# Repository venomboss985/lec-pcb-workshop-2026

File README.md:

# PCB Design Workshop

## Description
Learn how to use KiCad by designing your own PCB from scratch. During the workshops, you'll learn how most digital electronic devices get designed, schematic and layout best practices, and be able to assemble, test, and use your board to do something!

### What will be taught
* Basic KiCad usage
* Schematic best practices
* Layout best practices
* Using soldering irons, multimeters, and oscilloscopes

### What will NOT be taught
* Basic electrical theory (Ohms law, parallel/series, etc.)
* Firmware development (if firmware is needed, it will be provided)
* Datasheets (covered, not in depth)

## Prerequisites
* Some basic electrical knowledge (1 yr electrical or active LEC member)
* A laptop >4GB RAM with KiCad preinstalled
* git or GitHub Desktop and a GitHub account

## Rough Schedule
* Day 1 (3-4 hrs, hybrid): Anatomy of a PCB (by making a keychain light)
* Day 2 (3-4 hrs, hybrid): Project design (Start and hopefully finish the chosen project)
* Day 3 (2-3 hrs, in-person): Assemble and test your board (firmware will be provided if needed)

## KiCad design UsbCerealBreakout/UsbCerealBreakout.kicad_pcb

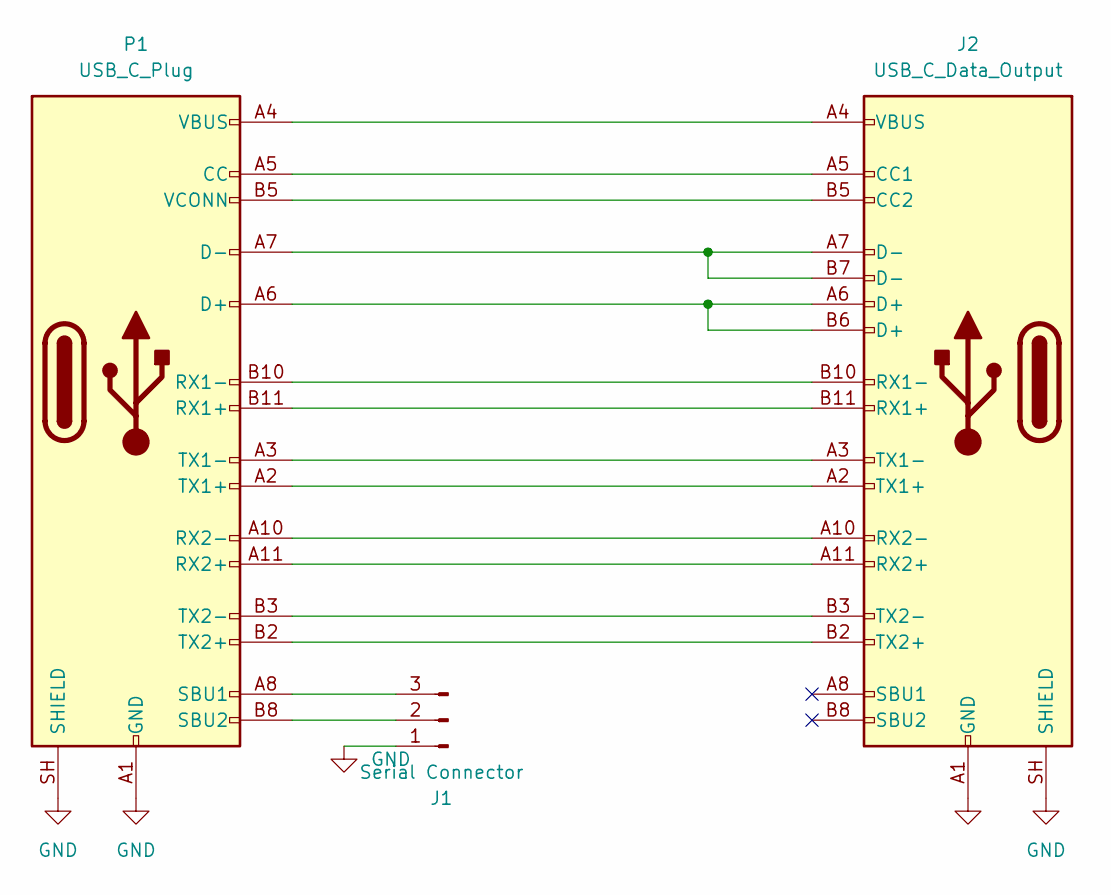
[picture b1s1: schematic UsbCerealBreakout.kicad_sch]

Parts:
J1: Serial Connector; PinSocket_1x03_P2.54mm_Vertical
J2: USB_C_Data_Output; USB_C_Receptacle_JAE_DX07S024WJ3R400
P1: USB_C_Plug; USB_C_Plug_Molex_105444

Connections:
GND: J1.1, J2.A1 (GND), J2.A12 (GND), J2.B1 (GND), J2.B12 (GND), J2.SH (SHIELD), P1.A1 (GND), P1.A12 (GND), P1.B1 (GND), P1.B12 (GND), P1.SH (SHIELD)
unnamed: J1.2, P1.B8 (SBU2)
unnamed: J1.3, P1.A8 (SBU1)
unnamed: J2.A5 (CC1), P1.A5 (CC)
unnamed: J2.B5 (CC2), P1.B5 (VCONN)
unnamed: J2.B11 (RX1+), P1.B11 (RX1+)
unnamed: J2.B10 (RX1-), P1.B10 (RX1-)
unnamed: J2.A11 (RX2+), P1.A11 (RX2+)
unnamed: J2.A10 (RX2-), P1.A10 (RX2-)
unnamed: J2.A2 (TX1+), P1.A2 (TX1+)
unnamed: J2.A3 (TX1-), P1.A3 (TX1-)
unnamed: J2.B2 (TX2+), P1.B2 (TX2+)
unnamed: J2.B3 (TX2-), P1.B3 (TX2-)
unnamed: J2.A4 (VBUS), J2.A9 (VBUS), J2.B4 (VBUS), J2.B9 (VBUS), P1.A4 (VBUS), P1.A9 (VBUS), P1.B4 (VBUS), P1.B9 (VBUS)
unnamed: J2.A6 (D+), J2.B6 (D+), P1.A6 (D+)
unnamed: J2.A7 (D-), J2.B7 (D-), P1.A7 (D-)

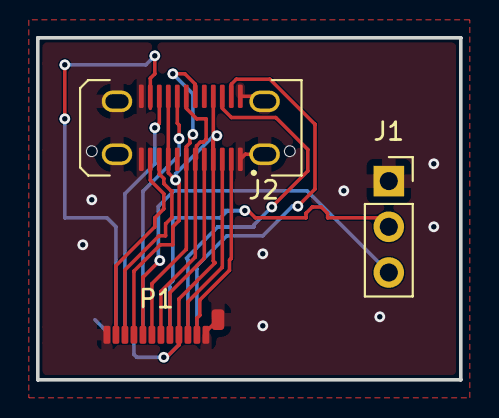
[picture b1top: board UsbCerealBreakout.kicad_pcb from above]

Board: 2 copper layers, 23.5 x 19.0 mm, 3 parts (0 on the bottom side), 16 nets.

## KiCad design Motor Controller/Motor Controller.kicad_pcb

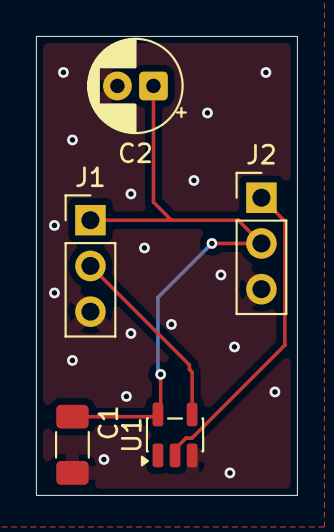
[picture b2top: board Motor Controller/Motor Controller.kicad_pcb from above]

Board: 2 copper layers, 14.5 x 25.5 mm, 5 parts (0 on the bottom side), 4 nets.

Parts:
C1: 100n; C_1206_3216Metric_Pad1.33x1.80mm_HandSolder
C2: 10u; CP_Radial_D5.0mm_P2.00mm
J1, J2: Conn_01x03_Pin; PinHeader_1x03_P2.54mm_Vertical
U1: SN74LV1T34DBV; SOT-23-5

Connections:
GND: C1.2, C2.2, J1.3, J2.3, U1.3 (GND)
unnamed: J1.2, U1.4 (Y)
unnamed: J2.1, U1.2 (A)
VBUS: C1.1, C2.1, J1.1, J2.2, U1.5 (VCC)

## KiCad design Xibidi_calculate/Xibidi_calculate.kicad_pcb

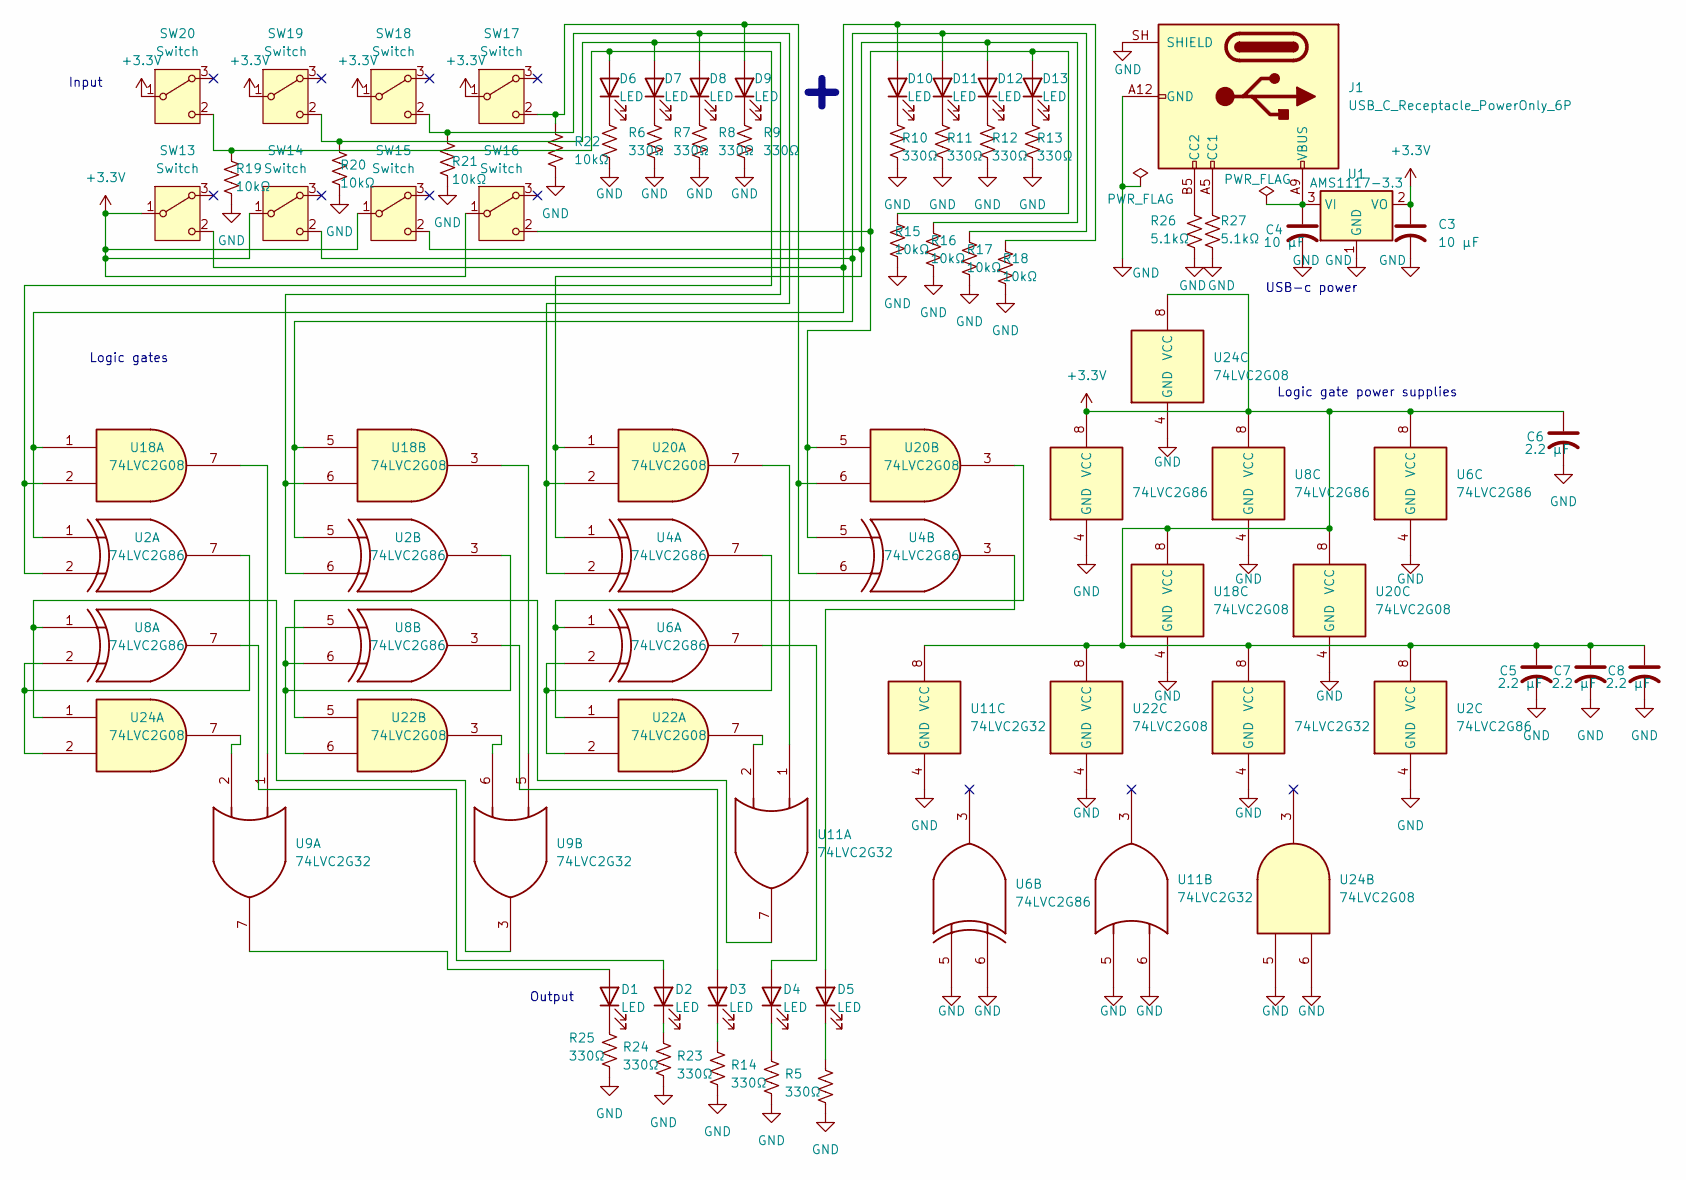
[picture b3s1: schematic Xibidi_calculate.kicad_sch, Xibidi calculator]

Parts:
C3, C4: 10 μF; C_0805_2012Metric
C5, C6, C7, C8: 2.2 μF; C_0805_2012Metric
D1, D2, D3, D4, D5, D6, D7, D8, D9, D10, D11, D12, D13: LED; LED_D5.0mm
J1: USB_C_Receptacle_PowerOnly_6P; USB_C_Receptacle_HRO_TYPE-C-31-M-17
R5, R6, R7, R8, R9, R10, R11, R12, R13, R14, R23, R24, R25: 330Ω; R_Axial_DIN0207_L6.3mm_D2.5mm_P7.62mm_Horizontal
R15, R16, R17, R18, R19, R20, R21, R22: 10kΩ; R_Axial_DIN0207_L6.3mm_D2.5mm_P7.62mm_Horizontal
R26, R27: 5.1kΩ; R_Axial_DIN0207_L6.3mm_D2.5mm_P7.62mm_Horizontal
SW13, SW14, SW15, SW16, SW17, SW18, SW19, SW20: Switch; SW_Slide-03_Wuerth-WS-SLTV_10x2.5x6.4_P2.54mm
U1: AMS1117-3.3; SOT-223-3_TabPin2
U2, U4, U6, U8: 74LVC2G86; TSSOP-8_3x3mm_P0.65mm
U9, U11: 74LVC2G32; TSSOP-8_3x3mm_P0.65mm
U18, U20, U22, U24: 74LVC2G08; TSSOP-8_3x3mm_P0.65mm

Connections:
+3.3V: C3.1, C5.1, C6.1, C7.1, C8.1, SW13.1 (B), SW14.1 (B), SW15.1 (B), SW16.1 (B), SW17.1 (B), SW18.1 (B), SW19.1 (B), SW20.1 (B), U1.2 (VO), U2.8 (VCC), U4.8 (VCC), U6.8 (VCC), U8.8 (VCC), U9.8 (VCC), U11.8 (VCC), U18.8 (VCC), U20.8 (VCC), U22.8 (VCC), U24.8 (VCC)
GND: C3.2, C4.2, C5.2, C6.2, C7.2, C8.2, J1.A12 (GND), J1.B12 (GND), J1.SH (SHIELD), R5.2, R6.2, R7.2, R8.2, R9.2, R10.2, R11.2, R12.2, R13.2, R14.2, R15.2, R16.2, R17.2, R18.2, R19.2, R20.2, R21.2, R22.2, R23.2, R24.2, R25.2, R26.2, R27.2, U1.1 (GND), U2.4 (GND), U4.4 (GND), U6.4 (GND), U6.5, U6.6, U8.4 (GND), U9.4 (GND), U11.4 (GND), U11.5, U11.6, U18.4 (GND), U20.4 (GND), U22.4 (GND), U24.4 (GND), U24.5, U24.6
unnamed: D1.2 (A), U9.7
unnamed: D1.1 (K), R25.1
unnamed: D2.2 (A), U8.7
unnamed: D2.1 (K), R24.1
unnamed: D3.2 (A), U8.3
unnamed: D3.1 (K), R23.1
unnamed: D4.2 (A), U6.7
unnamed: D4.1 (K), R14.1
unnamed: D5.2 (A), U4.3
unnamed: D5.1 (K), R5.1
unnamed: D6.2 (A), R19.1, SW20.2 (C), U2.2, U18.2
unnamed: D6.1 (K), R6.1
unnamed: D7.2 (A), R20.1, SW19.2 (C), U2.6, U18.6
unnamed: D7.1 (K), R7.1
unnamed: D8.2 (A), R21.1, SW18.2 (C), U4.2, U20.2
unnamed: D8.1 (K), R8.1
unnamed: D9.2 (A), R22.1, SW17.2 (C), U4.6, U20.6
unnamed: D9.1 (K), R9.1
unnamed: D10.2 (A), R18.1, SW13.2 (C), U2.1, U18.1
unnamed: D10.1 (K), R10.1
unnamed: D11.2 (A), R17.1, SW14.2 (C), U2.5, U18.5
unnamed: D11.1 (K), R11.1
unnamed: D12.2 (A), R16.1, SW15.2 (C), U4.1, U20.1
unnamed: D12.1 (K), R12.1
unnamed: D13.2 (A), R15.1, SW16.2 (C), U4.5, U20.5
unnamed: D13.1 (K), R13.1
unnamed: J1.A5 (CC1), R27.1
unnamed: J1.B5 (CC2), R26.1
unnamed: C4.1, J1.A9 (VBUS), J1.B9 (VBUS), U1.3 (VI)
unnamed: U2.3, U8.5, U8.6, U22.6
unnamed: U2.7, U8.2, U24.2
unnamed: U11.1, U20.7
unnamed: U11.2, U22.7
unnamed: U11.7, U22.5
unnamed: U9.5, U18.3
unnamed: U9.1, U18.7
unnamed: U6.1, U20.3, U22.1
unnamed: U4.7, U6.2, U22.2
unnamed: U9.6, U22.3
unnamed: U8.1, U9.3, U24.1
unnamed: U9.2, U24.7

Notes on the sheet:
Logic gate power supplies
Logic gates
Input
Output
USB-c power

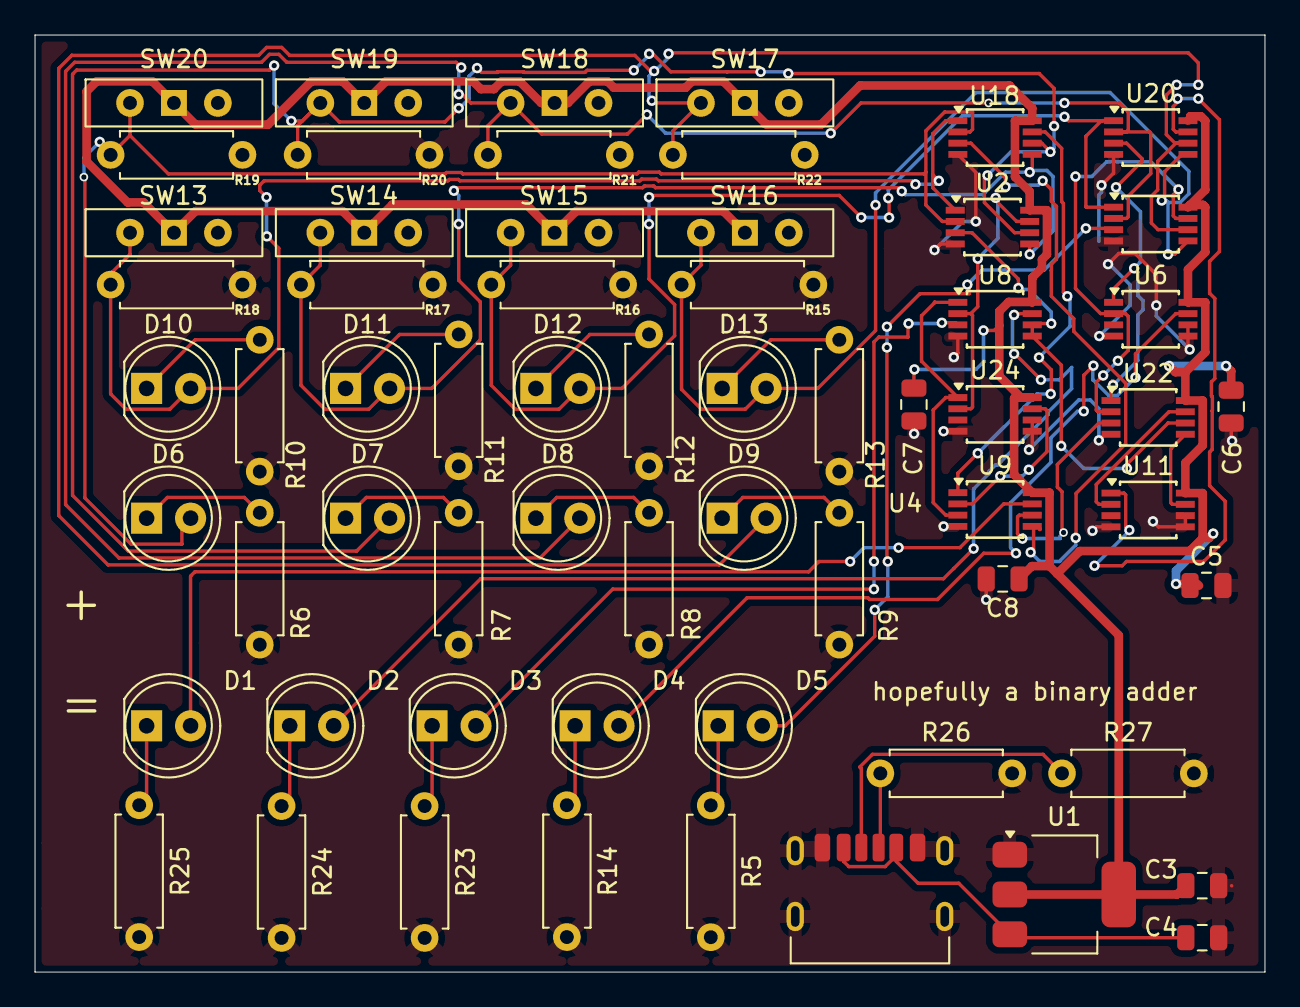
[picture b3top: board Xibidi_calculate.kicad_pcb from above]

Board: 2 copper layers, 71.1 x 54.2 mm, 62 parts (0 on the bottom side), 43 nets.

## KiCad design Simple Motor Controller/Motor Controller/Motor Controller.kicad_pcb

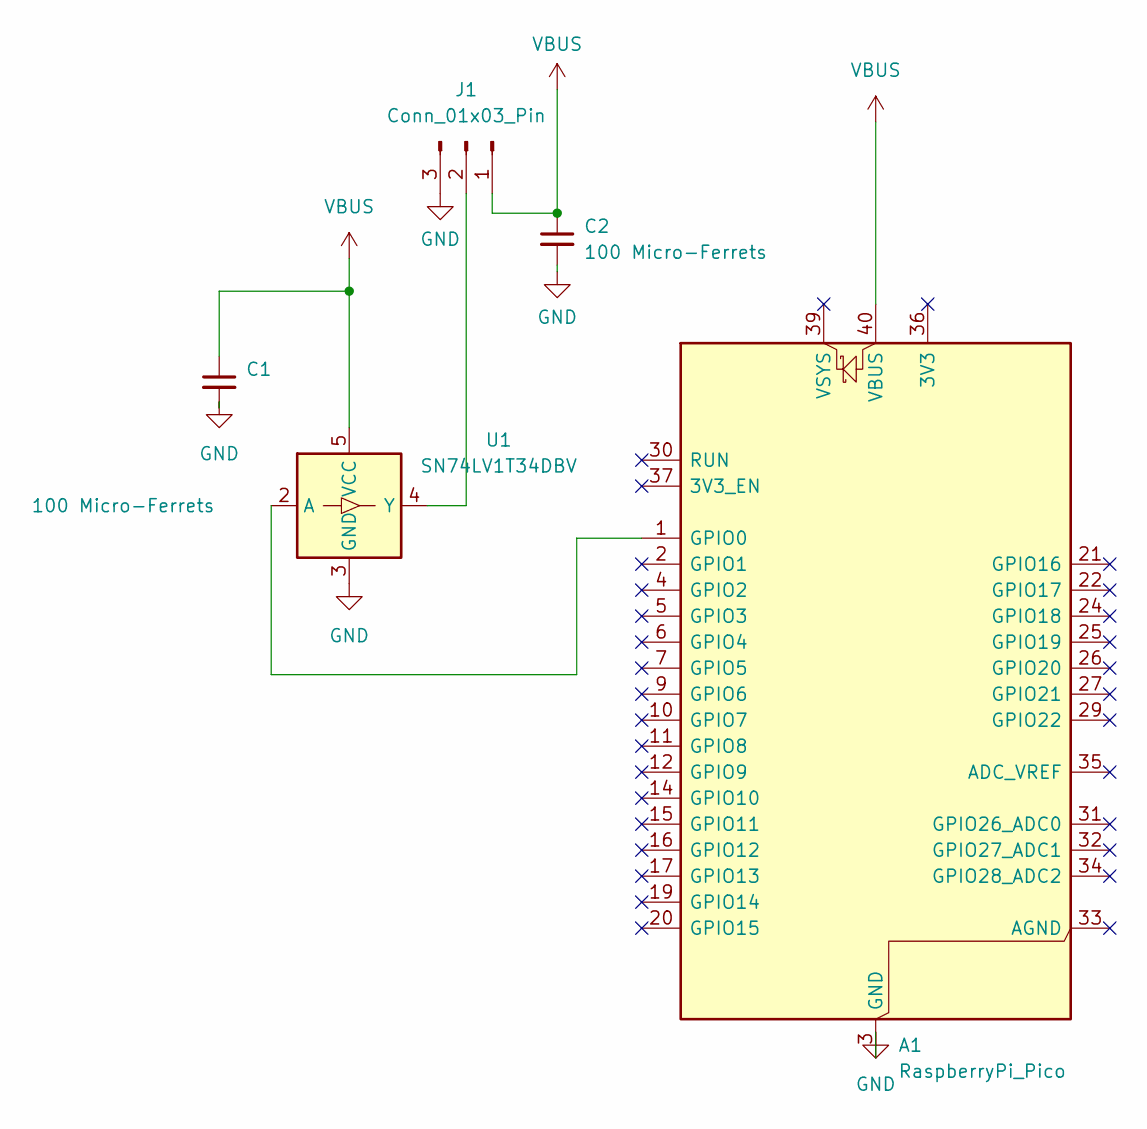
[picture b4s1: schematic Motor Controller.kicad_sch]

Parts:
A1: RaspberryPi_Pico; RaspberryPi_Pico_Common_Unspecified
C1: 100 Micro-Ferrets; C_1206_3216Metric_Pad1.33x1.80mm_HandSolder
C2: 100 Micro-Ferrets; CP_Radial_D5.0mm_P2.00mm
J1: Conn_01x03_Pin; PinHeader_1x03_P2.54mm_Vertical
U1: SN74LV1T34DBV; SOT-23-5

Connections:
GND: A1.3 (GND), A1.8 (GND), A1.13 (GND), A1.18 (GND), A1.23 (GND), A1.28 (GND), A1.38 (GND), C1.2, C2.2, J1.3, U1.3 (GND)
unnamed: A1.1 (GPIO0), U1.2 (A)
unnamed: J1.2, U1.4 (Y)
VBUS: A1.40 (VBUS), C1.1, C2.1, J1.1, U1.5 (VCC)

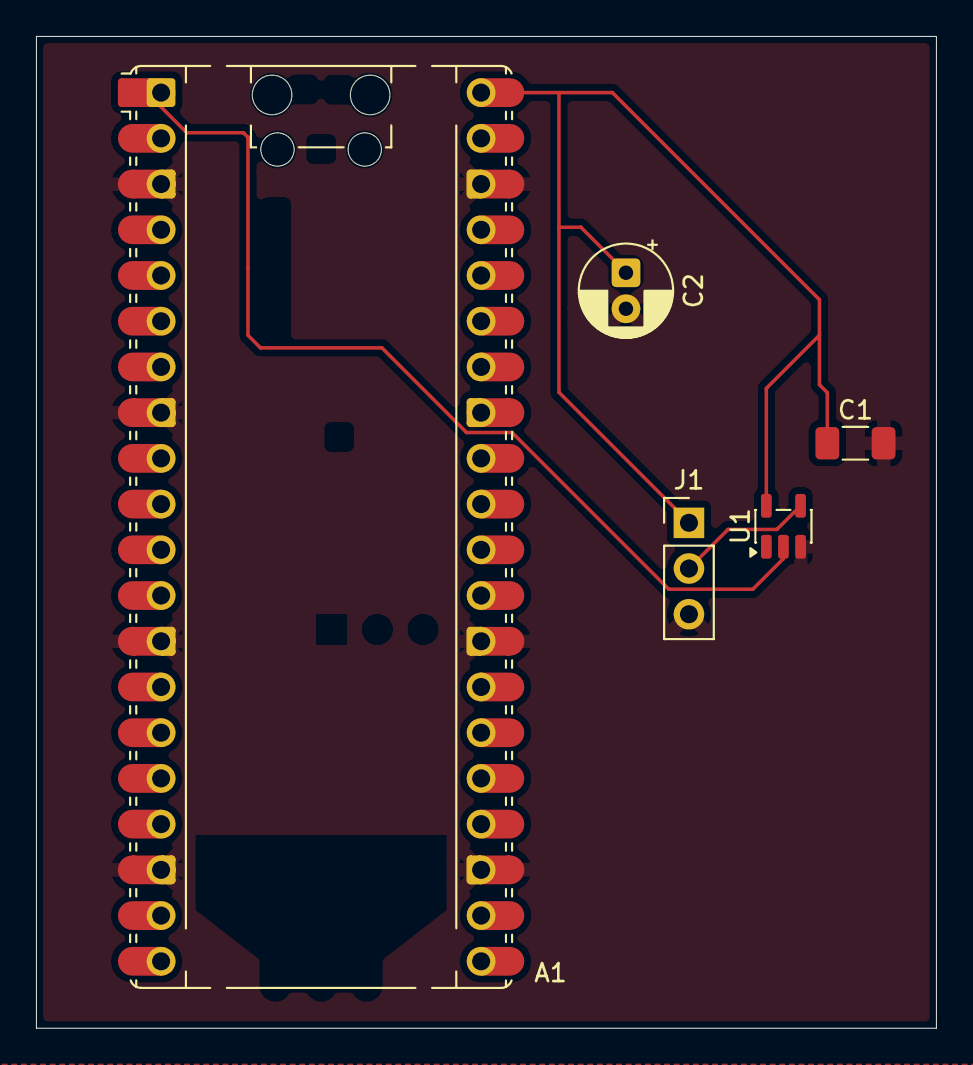
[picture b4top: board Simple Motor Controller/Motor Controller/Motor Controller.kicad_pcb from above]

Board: 2 copper layers, 50.0 x 55.1 mm, 5 parts (0 on the bottom side), 4 nets.

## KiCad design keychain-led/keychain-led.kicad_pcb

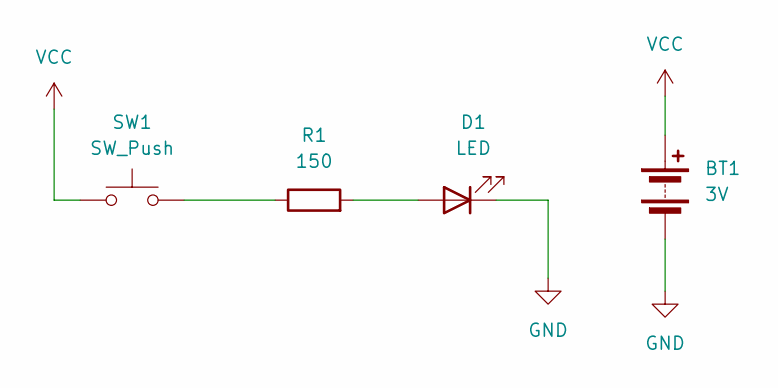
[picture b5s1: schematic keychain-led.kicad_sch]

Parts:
BT1: 3V; BatteryHolder_Keystone_1058_1x2032
D1: LED; LED_D5.0mm-3
R1: 150; R_Axial_DIN0207_L6.3mm_D2.5mm_P7.62mm_Horizontal
SW1: SW_Push; SW_PUSH_6mm

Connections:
GND: BT1.2 (-), D1.1 (K)
unnamed: D1.2 (A), R1.2
unnamed: R1.1, SW1.2
VCC: BT1.1 (+), SW1.1

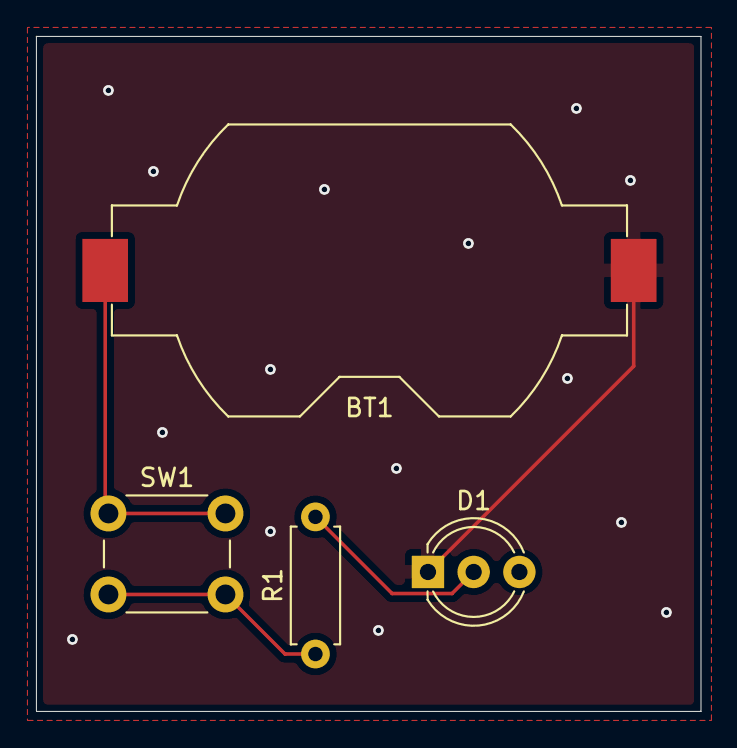
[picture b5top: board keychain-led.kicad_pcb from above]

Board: 2 copper layers, 36.9 x 37.5 mm, 4 parts (0 on the bottom side), 4 nets.
